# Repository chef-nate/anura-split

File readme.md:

# anura-split

## 34 (+2) key split mechanical keyboard featuring

- hotswap choc v1 switches
- fully reversible pcb
- bluetooth support with nice!nano
- support for nice!view
- support for cirque trackpad (requires breakout board off nice!view headers)
- rotary scroll encoder switch (SW18, outer thumb cluster key)

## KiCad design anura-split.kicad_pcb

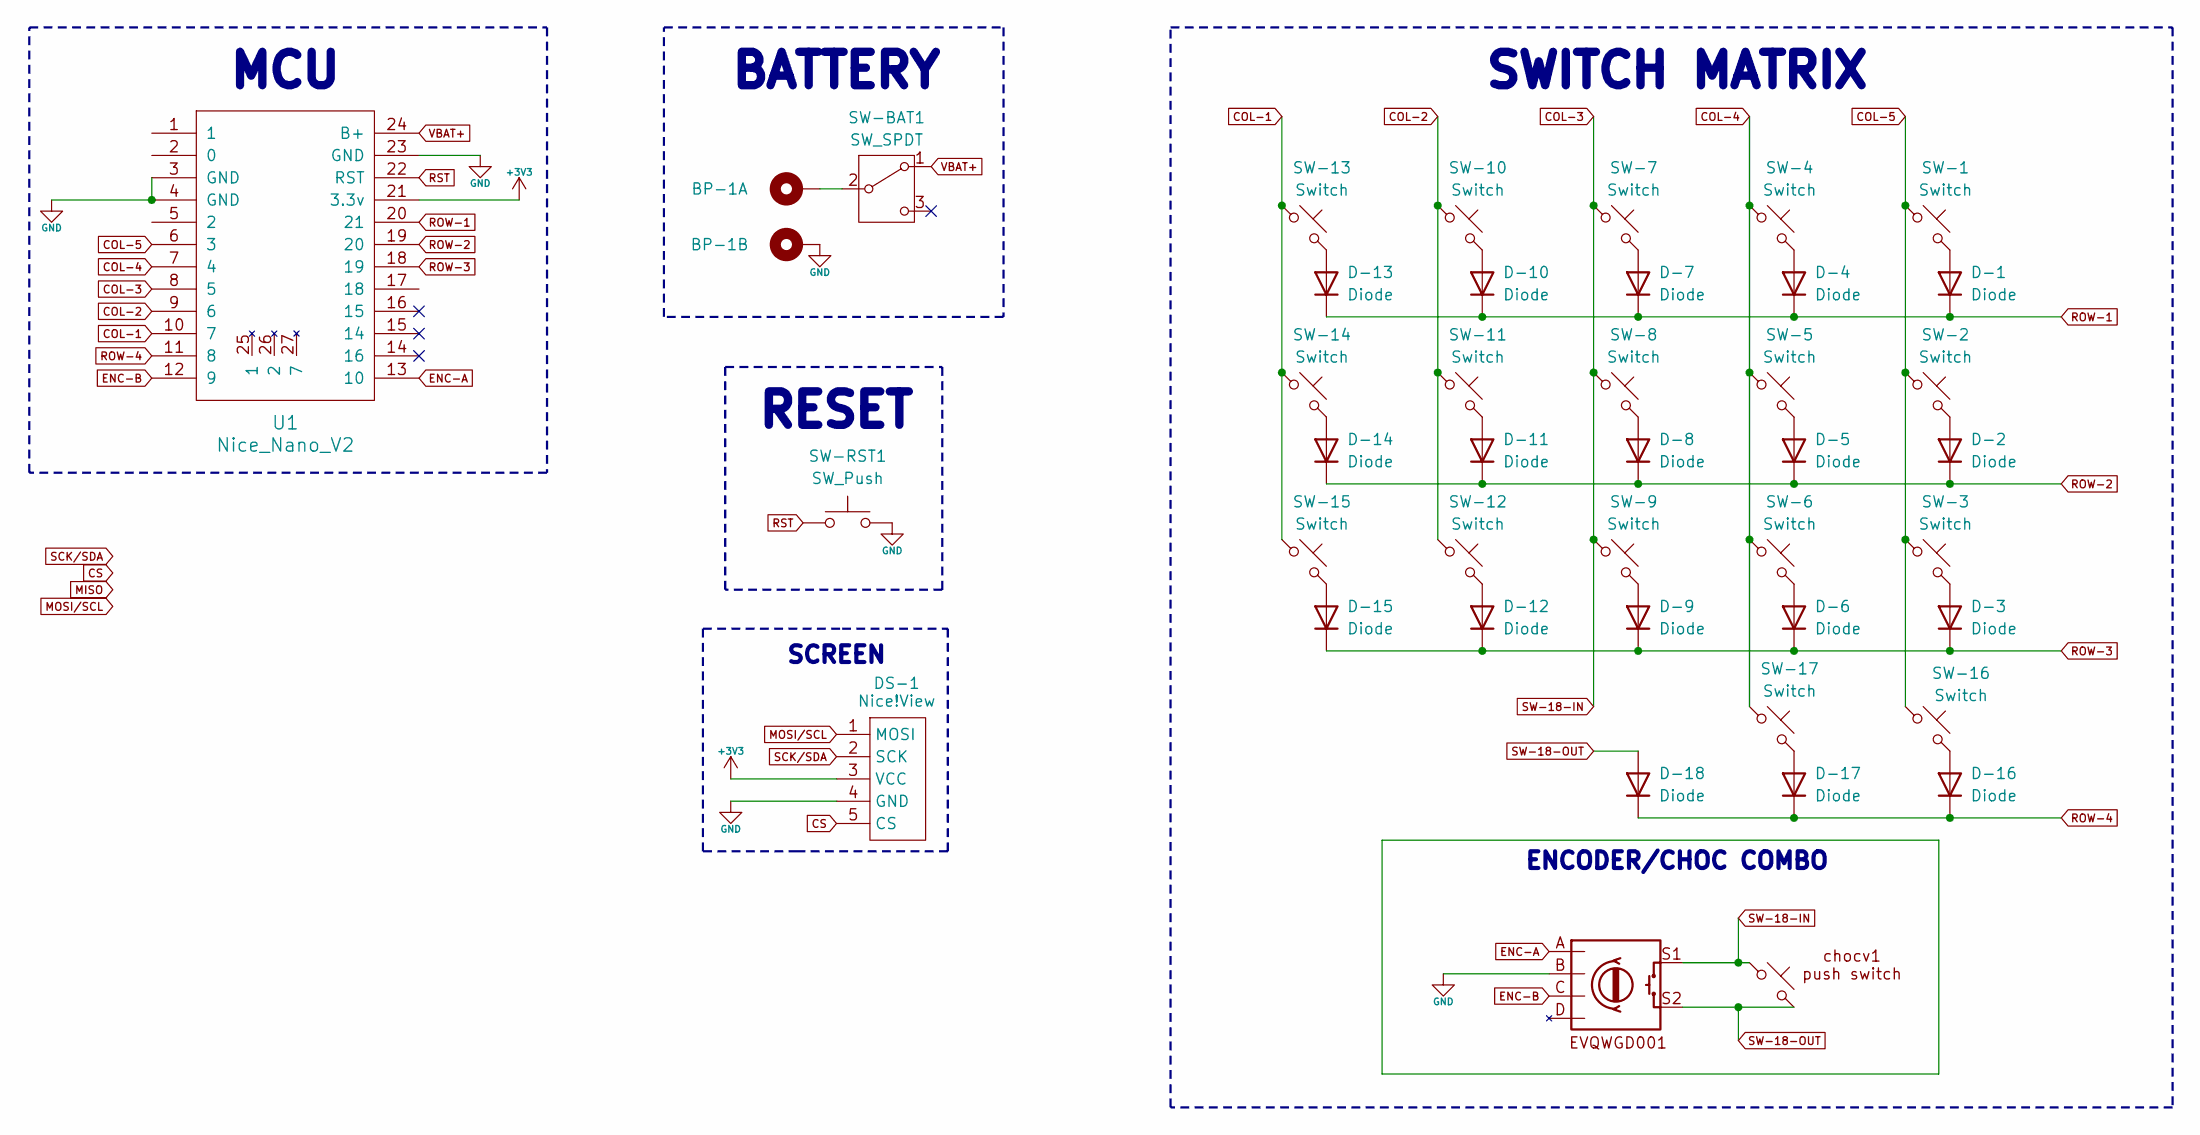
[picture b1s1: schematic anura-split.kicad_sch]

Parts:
BP-1: BatteryPad
CombChocEncoder1: hotswap_chocv1_combined_EVQWGD001
D-1, D-2, D-3, D-4, D-5, D-6, D-7, D-8, D-9, D-10, D-11, D-12, D-13, D-14, D-15, D-16, D-17, D-18: Diode; SOD123 Reversible
DS-1: Nice!View; nice!view_rev2
SW-1, SW-2, SW-3, SW-4, SW-5, SW-6, SW-7, SW-8, SW-9, SW-10, SW-11, SW-12, SW-13, SW-14, SW-15, SW-16, SW-17: Switch; Choc_Hotswap_Reversible
SW-BAT1: SW_SPDT; SW-TH_MSK12C02
SW-RST1: SW_Push; SW_PUSH_SPST
U1: Nice_Nano_V2; nice!nano_facedown

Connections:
+3V3: DS-1.3 (VCC), U1.21 (3.3v)
COL-1: SW-13.1, SW-14.1, SW-15.1, U1.10 (7)
COL-2: SW-10.1, SW-11.1, SW-12.1, U1.9 (6)
COL-3: CombChocEncoder1.1, CombChocEncoder1.S1, SW-7.1, SW-8.1, SW-9.1, U1.8 (5)
COL-4: SW-4.1, SW-5.1, SW-6.1, SW-17.1, U1.7 (4)
COL-5: SW-1.1, SW-2.1, SW-3.1, SW-16.1, U1.6 (3)
CS: DS-1.5 (CS)
ENC-A: CombChocEncoder1.A, U1.13 (10)
ENC-B: CombChocEncoder1.C, U1.12 (9)
GND: BP-1.2, CombChocEncoder1.B, DS-1.4 (GND), SW-RST1.2, U1.3 (GND), U1.4 (GND), U1.23 (GND)
MOSI/SCL: DS-1.1 (MOSI)
unnamed: D-1.2 (A), SW-1.2
unnamed: D-2.2 (A), SW-2.2
unnamed: D-3.2 (A), SW-3.2
unnamed: D-4.2 (A), SW-4.2
unnamed: D-5.2 (A), SW-5.2
unnamed: D-6.2 (A), SW-6.2
unnamed: D-7.2 (A), SW-7.2
unnamed: D-8.2 (A), SW-8.2
unnamed: D-9.2 (A), SW-9.2
unnamed: D-10.2 (A), SW-10.2
unnamed: D-11.2 (A), SW-11.2
unnamed: D-12.2 (A), SW-12.2
unnamed: D-13.2 (A), SW-13.2
unnamed: D-14.2 (A), SW-14.2
unnamed: D-15.2 (A), SW-15.2
unnamed: D-16.2 (A), SW-16.2
unnamed: D-17.2 (A), SW-17.2
unnamed: BP-1.1, SW-BAT1.2 (B)
ROW-1: D-1.1 (K), D-4.1 (K), D-7.1 (K), D-10.1 (K), D-13.1 (K), U1.20 (21)
ROW-2: D-2.1 (K), D-5.1 (K), D-8.1 (K), D-11.1 (K), D-14.1 (K), U1.19 (20)
ROW-3: D-3.1 (K), D-6.1 (K), D-9.1 (K), D-12.1 (K), D-15.1 (K), U1.18 (19)
ROW-4: D-16.1 (K), D-17.1 (K), D-18.1 (K), U1.11 (8)
RST: SW-RST1.1, U1.22 (RST)
SCK/SDA: DS-1.2 (SCK)
SW-18-OUT: CombChocEncoder1.2, CombChocEncoder1.S2, D-18.2 (A)
VBAT+: SW-BAT1.1 (A), U1.24 (B+)

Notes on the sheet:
SCREEN
RESET
MCU
ENCODER/CHOC COMBO
BATTERY
SWITCH MATRIX

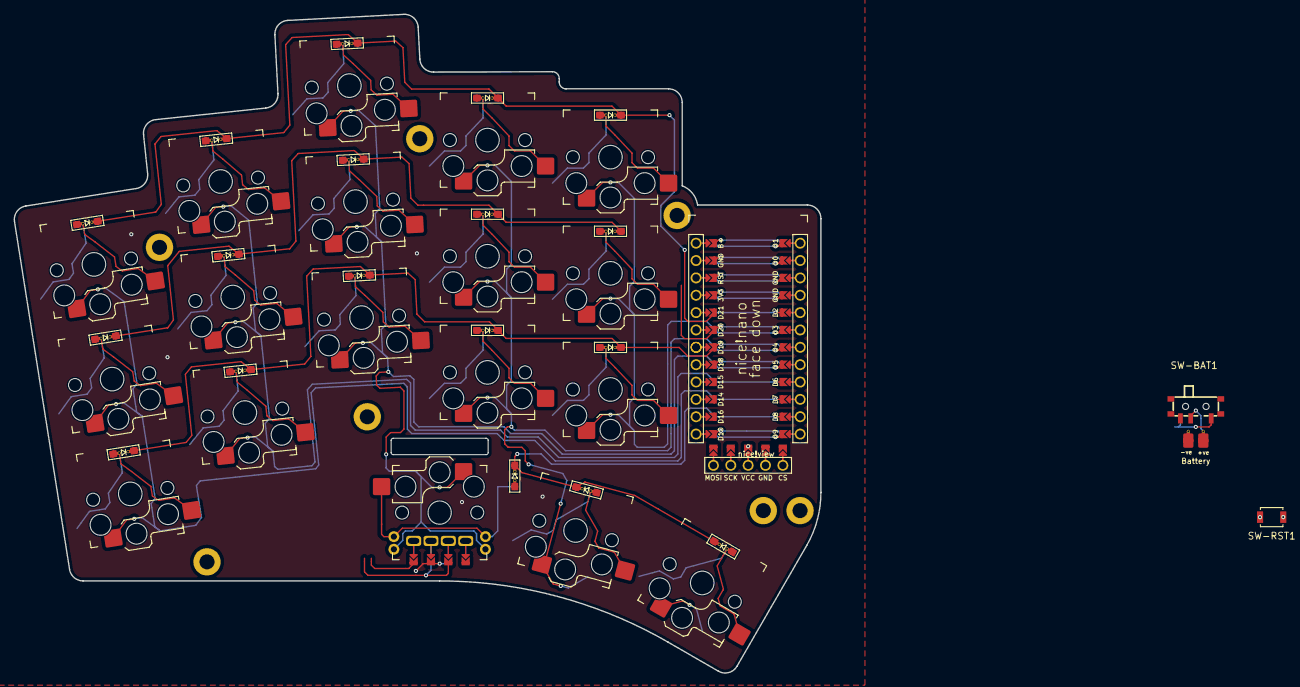
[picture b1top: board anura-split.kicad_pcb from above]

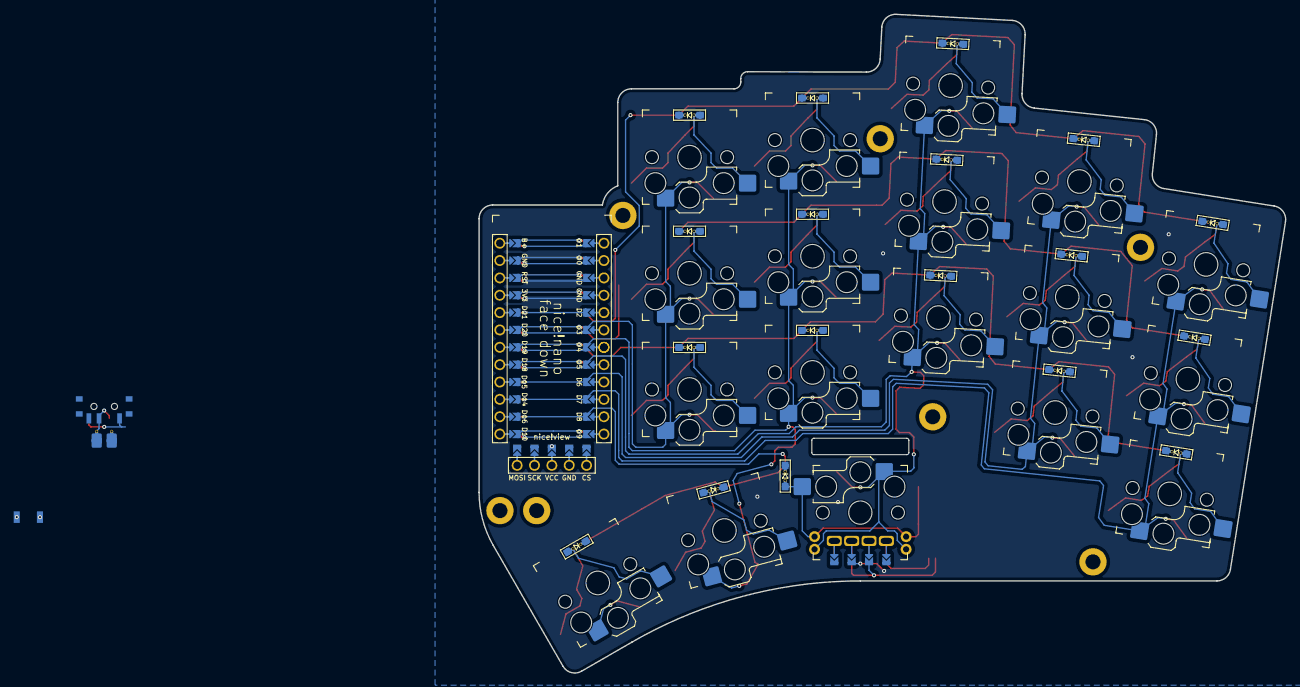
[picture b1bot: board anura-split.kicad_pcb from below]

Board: 2 copper layers, 118.0 x 96.4 mm, 41 parts (19 on the bottom side), 34 nets.

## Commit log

2025-08-15 initial commit
    schematic designed and basic pcb design started. still wip
2025-08-15 added readme
    added readme with project overview
2025-08-15 lib-anura updates
    added and updated variety of symbols in schematic library, to get rid of
    dependencies
2025-08-15 3d models added
    removed dependencies for 3d models and instead integrated directly into
    project
2025-08-16 trace routing + silkscreen design
2025-08-18 routing + schematic changes
    mcu nets reorganised to suit trace routing better, and more traces
    routed
